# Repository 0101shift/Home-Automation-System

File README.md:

# Home-Automation-System
The project aims in setting up a sensor network interface where the user can sense, track and control their devices with a simple GUI. The sensor network consists of a small sensing &amp; control unit called as slave node which is connected to a Master through RS485 bus. Each master is capable of controlling up to 16 slave nodes and all the Masters are connected to cloud for wireless data access.

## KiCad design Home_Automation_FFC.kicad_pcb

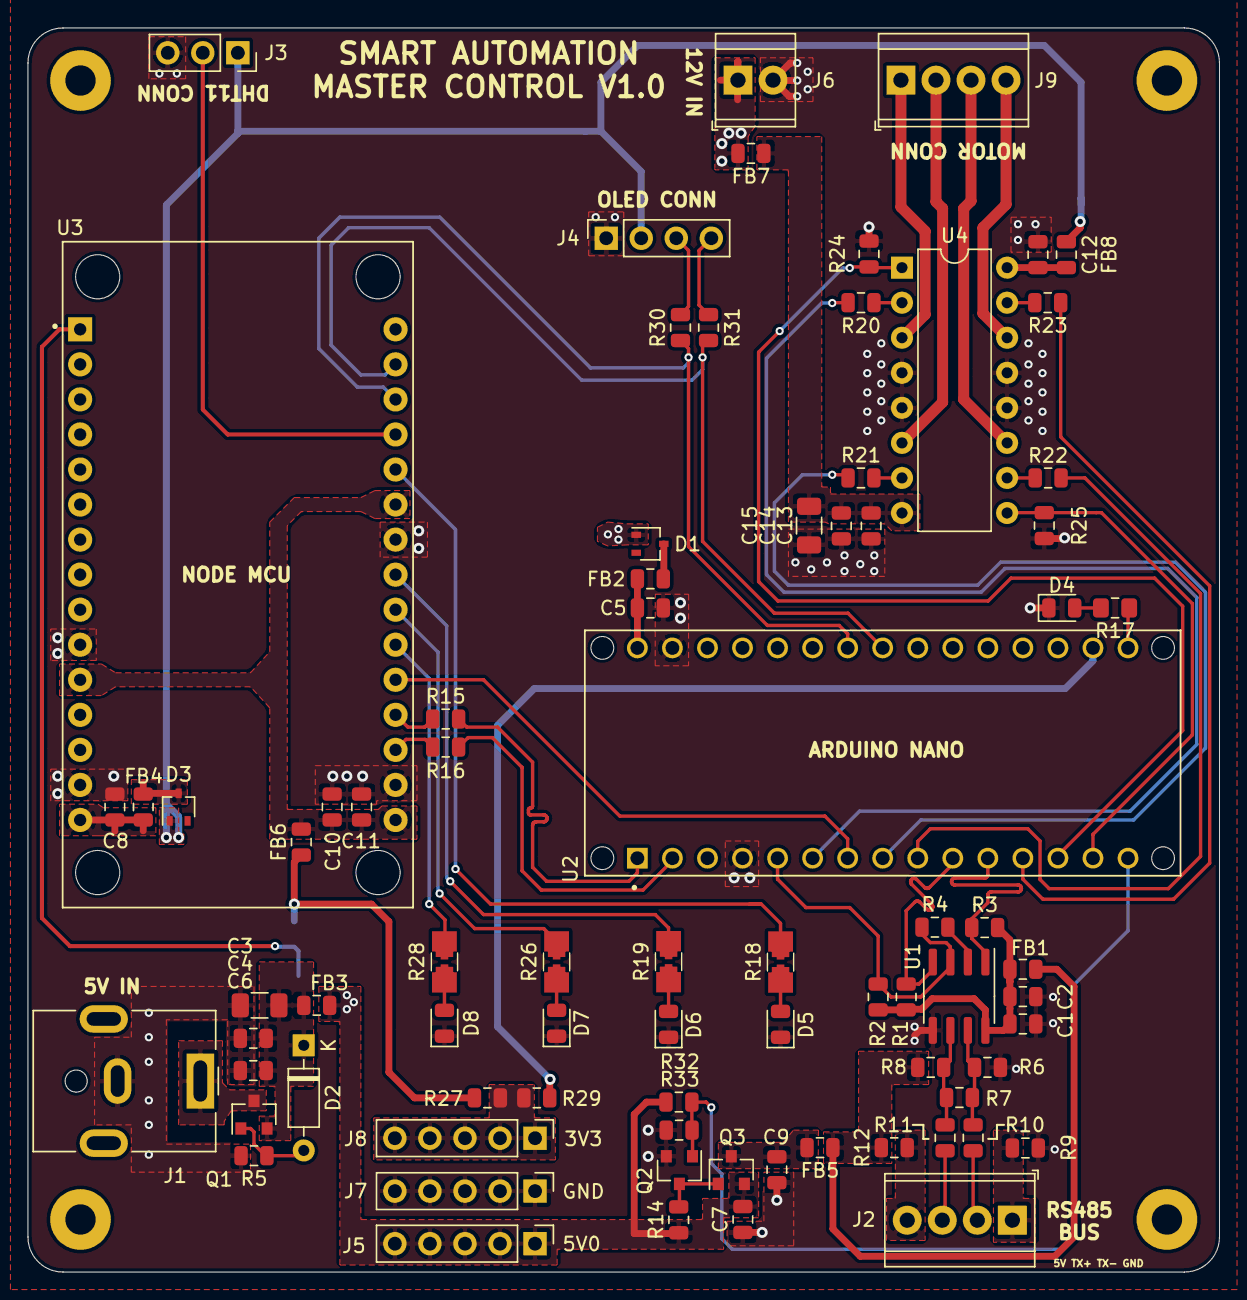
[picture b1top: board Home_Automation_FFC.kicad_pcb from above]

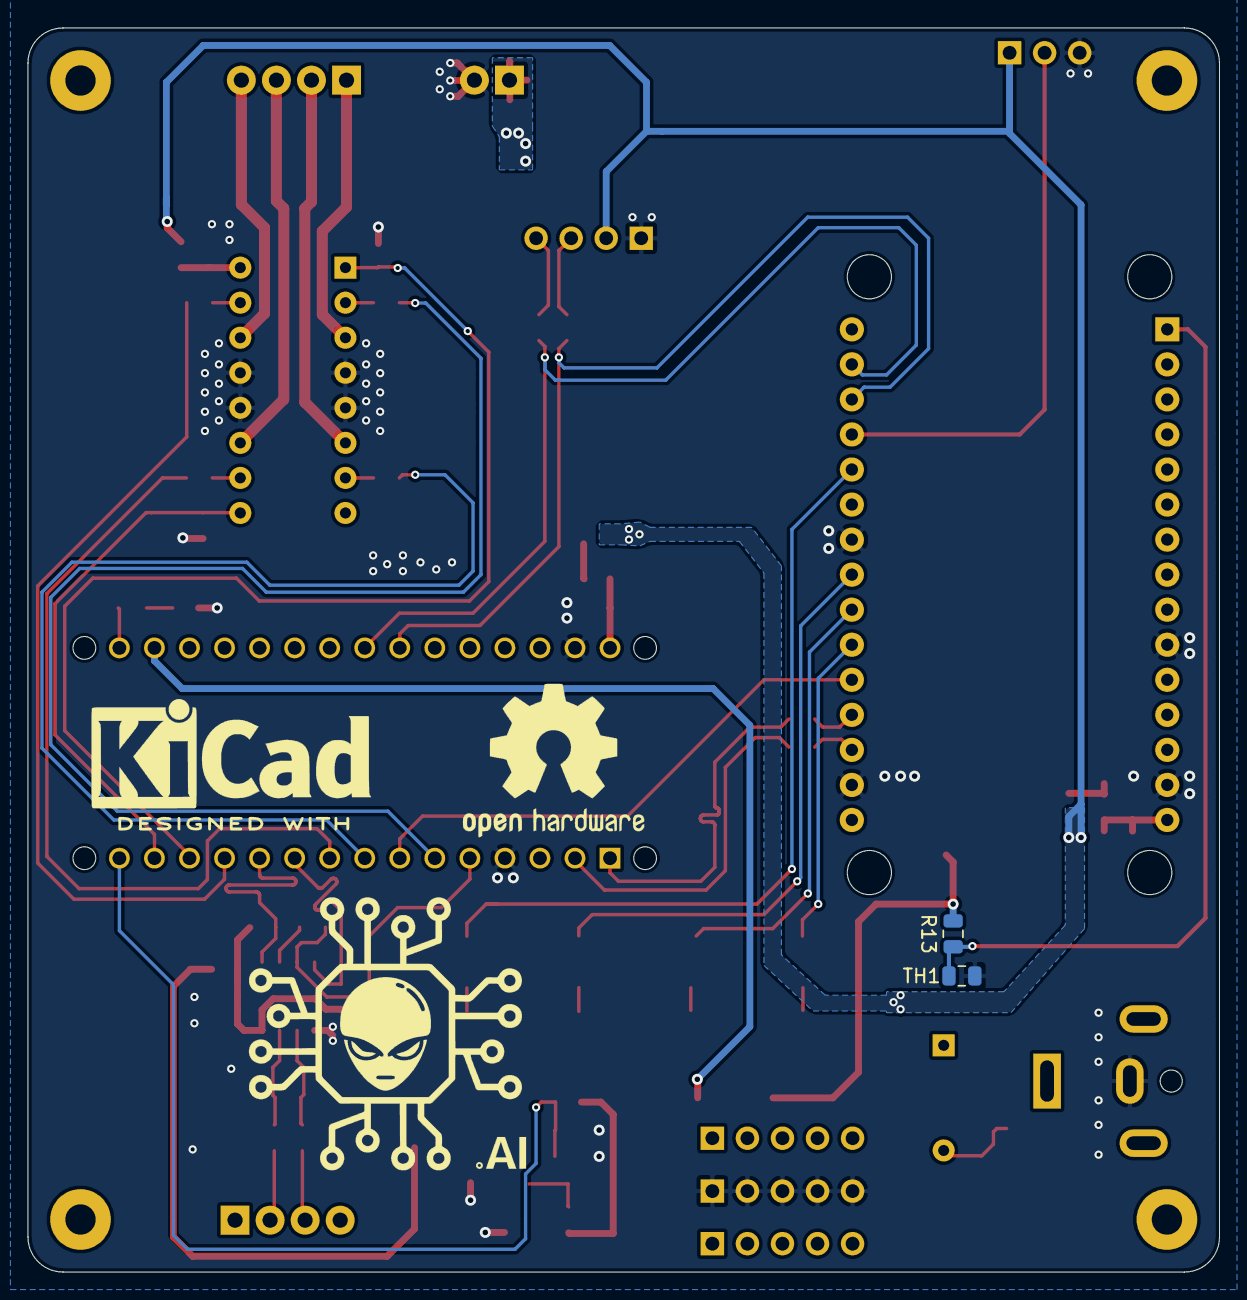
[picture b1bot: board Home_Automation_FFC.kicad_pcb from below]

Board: 2 copper layers, 86.4 x 90.2 mm, 85 parts (2 on the bottom side), 66 nets.

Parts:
C1, C6, C8, C11, C12, C13: 0.1u; C_0805_2012Metric
C2, C4, C9, C10, C14: 10u; C_0805_2012Metric
C3, C15: 100u; C_1206_3216Metric
C5: 0.1U; C_0805_2012Metric
C7: 1u; C_0805_2012Metric
D1, D3: BAT54W; SOT-323_SC-70
D2: 1N5231; D_DO-35_SOD27_P7.62mm_Horizontal
D4, D5, D6, D7, D8: LED; LED_0805_2012Metric
FB1, FB2, FB3, FB4, FB5, FB6, FB7, FB8: 30E; L_0805_2012Metric
H1, H2, H3, H4: MountingHole_Pad; MountingHole_2.2mm_M2_Pad
J1: Barrel_Jack; BarrelJack_CUI_PJ-063AH_Horizontal
J2, J9: Screw_Terminal_01x04; TerminalBlock_TE_282834-4_1x04_P2.54mm_Horizontal
J3: Conn_01x03_Female; PinSocket_1x03_P2.54mm_Vertical
J4: Conn_01x04_Female; PinSocket_1x04_P2.54mm_Vertical
J5, J7, J8: Conn_01x05_Male; PinHeader_1x05_P2.54mm_Vertical
J6: Screw_Terminal_01x02; TerminalBlock_TE_282834-2_1x02_P2.54mm_Horizontal
Q1, Q3: DMG2301L; SOT-23
Q2: 2N7002; SOT-23
R1, R2, R3, R13, R14, R24, R25, R32: 10k; R_0805_2012Metric
R4, R9, R10, R11, R12, R15, R16, R20, R21, R22, R23, R29, R30, R31: 0E; R_0805_2012Metric
R5: 100k; R_0805_2012Metric
R6, R8: 20k; R_0805_2012Metric
R7: 120E; R_0805_2012Metric
R17: 1.2k; R_0805_2012Metric_Pad1.15x1.40mm_HandSolder
R18, R19, R26, R28: 1.2k; R-FFP_1206-0402
R27, R33: DNI; R_0805_2012Metric
TH1: 100K; R_0805_2012Metric
U1: MAX485E; SOIC-8_3.9x4.9mm_P1.27mm
U2: NANO; Arduino_nano
U3: NODEMCU; Nodemcu
U4: L293D; DIP-16_W7.62mm

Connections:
3V3_OUT: FB6.1, R13.1, R27.1
5V0: C7.2, D1.1, D3.1, FB3.1, FB8.2, J3.1, J4.2, J5.1, J5.2, J5.3, J5.4, J5.5, Q3.2, R14.1, R32.1
5V0_IN1: D1.3, FB2.1
5V0_IN2: D3.3, FB4.2
5V0_OUT: FB1.1, FB5.1, R8.1, R12.1
12V: C13.1, C14.1, C15.1, FB7.1, U4.8
/3V3_AUX: R29.1, U2.17
/5V_EN: Q2.1, R32.2, R33.1, U2.15
/A_EN: R24.1, U2.13, U4.1
/B_EN: R25.1, U2.14, U4.9
/D4: R18.1, U3.26
/D5: R19.1, U3.23
/D6: R26.1, U3.22
/D8: R28.1, U3.21
/D13: R17.1, U2.16
/DI: R1.1, U1.4, U2.10
/I2C_SCL: R30.1, U2.24, U3.28
/I2C_SDA: R31.1, U2.23, U3.29
/MOT_A+: R20.1, U2.6
/MOT_A-: R21.1, U2.8
/MOT_B+: R22.1, U2.9
/MOT_B-: R23.1, U2.12
/READY: U2.7, U3.20
/RO: R3.1, U1.1, U2.11
/RS485_TX+: R7.1, R8.2, R11.1, U1.6
/RS_485_TX-: R6.1, R7.2, R10.1, U1.7
/RX: R15.2, U2.1
/TEMP_IN: J3.2, U3.27
/TX: R16.2, U2.2
/WE: R2.1, R4.1, U1.3, U2.5
GND: C1.2, C2.2, C3.2, C4.2, C5.2, C6.2, C7.1, C8.2, C9.1, C10.2, C11.2, C12.2, C13.2, C14.2, C15.2, D4.1, D5.1, D6.1, D7.1, D8.1, J1.2, J3.3, J4.1, J6.2, J7.1, J7.2, J7.3, J7.4, J7.5, Q2.2, R5.2, R6.2, R9.1, R24.2, R25.2, R33.2, TH1.2, U1.5, U2.4, U2.29, U3.10, U3.14, U3.17, U3.24, U4.4, U4.5, U4.12, U4.13
unnamed: C1.1, C2.1, FB1.2, R1.2, R2.2, R3.2, U1.8
unnamed: C3.1, C4.1, C6.1, D2.1, FB3.2, Q1.2
unnamed: C5.1, FB2.2, U2.30
unnamed: C8.1, FB4.1, U3.15
unnamed: C9.2, FB5.2, Q3.3
unnamed: C10.1, C11.1, FB6.2, U3.11, U3.16, U3.25
unnamed: C12.1, FB8.1, U4.16
unnamed: D2.2, Q1.1, R5.1
unnamed: D4.2, R17.2
unnamed: D5.2, R18.2
unnamed: D6.2, R19.2
unnamed: D7.2, R26.2
unnamed: D8.2, R28.2
unnamed: FB7.2, J6.1
unnamed: J1.1, Q1.3
unnamed: J2.1, R9.2
unnamed: J2.2, R10.2
unnamed: J2.3, R11.2
unnamed: J2.4, R12.2
unnamed: J4.3, R30.2
unnamed: J4.4, R31.2
unnamed: J8.1, J8.2, J8.3, J8.4, J8.5, R27.2, R29.2
unnamed: J9.1, U4.3
unnamed: J9.2, U4.6
unnamed: J9.3, U4.11
unnamed: J9.4, U4.14
unnamed: Q2.3, Q3.1, R14.2
unnamed: R4.2, U1.2
unnamed: R13.2, TH1.1, U3.1
unnamed: R15.1, U3.19
unnamed: R16.1, U3.18
unnamed: R20.2, U4.2
unnamed: R21.2, U4.7
unnamed: R22.2, U4.10
unnamed: R23.2, U4.15

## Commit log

2022-06-18 Add files via upload
    Added project design files
2022-06-18 Update README.md
    Added Image
2022-06-18 Add files via upload
    Added gerber file
2022-06-20 Add files via upload
    Added Design in .pdf format
